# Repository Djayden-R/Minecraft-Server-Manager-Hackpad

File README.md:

# Minecraft Server Manager Hackpad

This is a hackpad designed to control a Minecraft server. It has keys to interact with the server and device: a start key and two keys to switch between modes. It will indicate the state of the server using a status LED and has a screen that displays the live chat and other information about the server.

A demonstraction video can be found [here](https://youtu.be/SgViQMdPCGE) and the build process is documented [here](https://blueprint.hackclub.com/projects/6261).

## Why did I make it?

I have a Minecraft server with my friends and often don't notice it when my friends are online, so I wanted to make this device to show when my friends go online.

Couldn't I just make a Discord bot to ping me when my friends go online? Yeah, but it wouldn't be as fun as making a special device for on my desk that also shows the Minecraft chat live.

## How does it work?

The main logic of checking the server status and the chat isn't done on the Hackpad itself, but instead on the computer it is connected to. To make this work the pc will need to run the ```host.py```. This is going to connect with Home Assistant via MQTT. There is a Home Assistant automation needed that sends the information to the correct MQTT topics.
The program can send the following to the Hackpad (over USB):

- LED [COLOR]
- STATUS [STATUS] [PLAYERS] [VERSION] [UPTIME]
- CHAT [LAST_MESSAGE]
- LOG [LOGLINE]
- MODE [MODE]

The Hackpads task is to handle displaying text on the LCD, handle the LED and send the button presses (either LONG or SHORT):

- START
- MODE_NEXT
- MODE_PREV

Also, about the LED, the hackpad displays different colors in different situations:

- Server off > Red
- Server booting > Blinking Orange
- Server on > Blue
- People online > Blinking Green

## Hardware

Schematic                               |  PCB                   |   3D model
:--------------------------------------:|:----------------------:|:-------------------------:
 |  | 

## BOM

- 3x Cherry MX Switches
- 3x DSA Keycaps
- 1x SK6812 MINI-E LED
- 1x 0.91" 128x32 OLED Display
- 1x XIAO RP2040
- 1x Case (2 printed parts)

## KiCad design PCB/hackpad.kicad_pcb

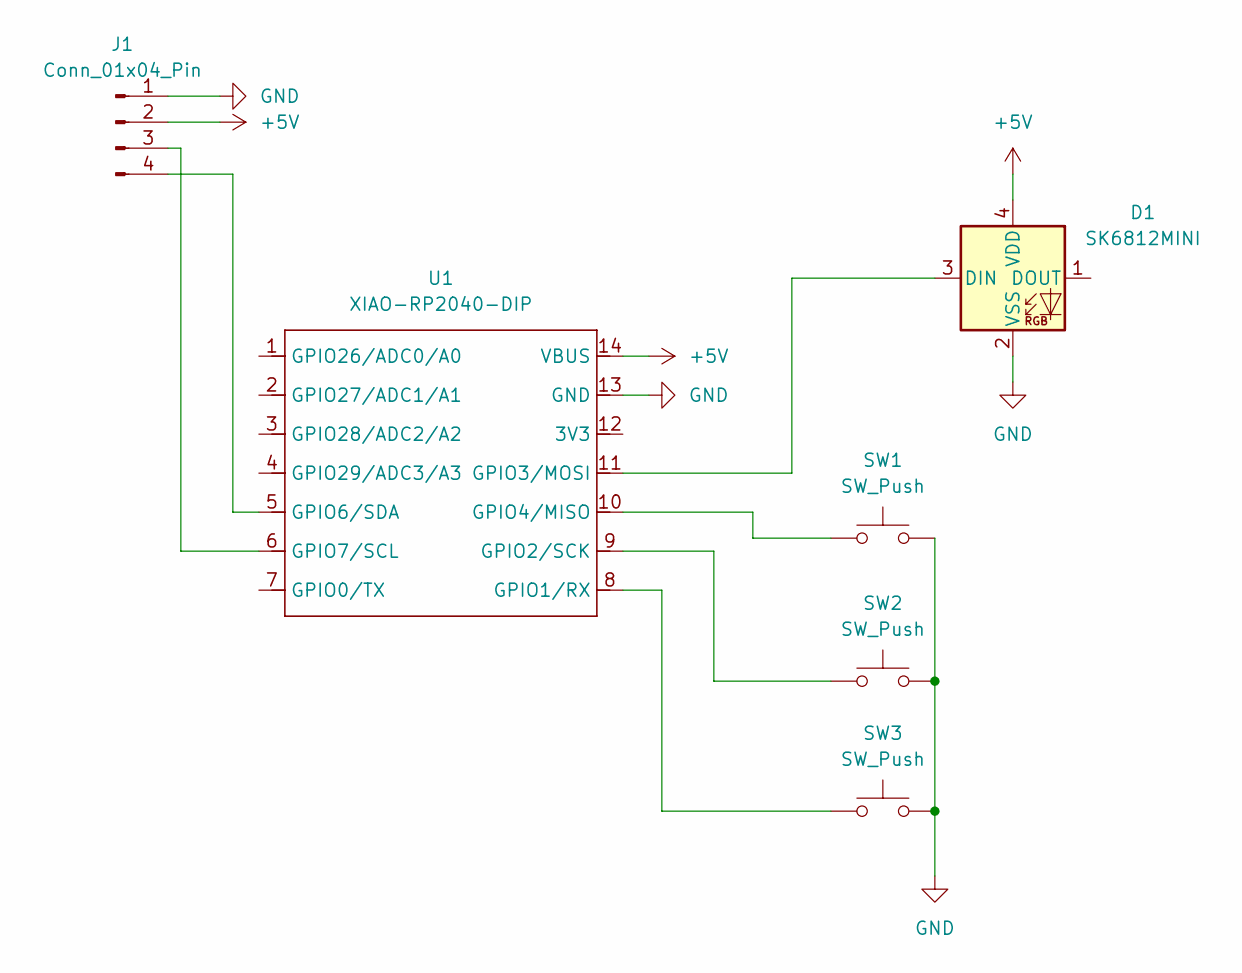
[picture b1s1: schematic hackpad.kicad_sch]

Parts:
D1: SK6812MINI; LED_SK6812MINI_PLCC4_3.5x3.5mm_P1.75mm
J1: Conn_01x04_Pin; SSD1306-0.91-OLED-4pin-128x32
SW1, SW2, SW3: SW_Push; SW_Cherry_MX_1.00u_PCB
U1: XIAO-RP2040-DIP

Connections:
+5V: D1.4 (VDD), J1.2, U1.14 (VBUS)
GND: D1.2 (VSS), J1.1, SW1.2, SW2.2, SW3.2, U1.13 (GND)
unnamed: D1.3 (DIN), U1.11 (GPIO3/MOSI)
unnamed: J1.3, U1.6 (GPIO7/SCL)
unnamed: J1.4, U1.5 (GPIO6/SDA)
unnamed: SW3.1, U1.8 (GPIO1/RX)
unnamed: SW2.1, U1.9 (GPIO2/SCK)
unnamed: SW1.1, U1.10 (GPIO4/MISO)

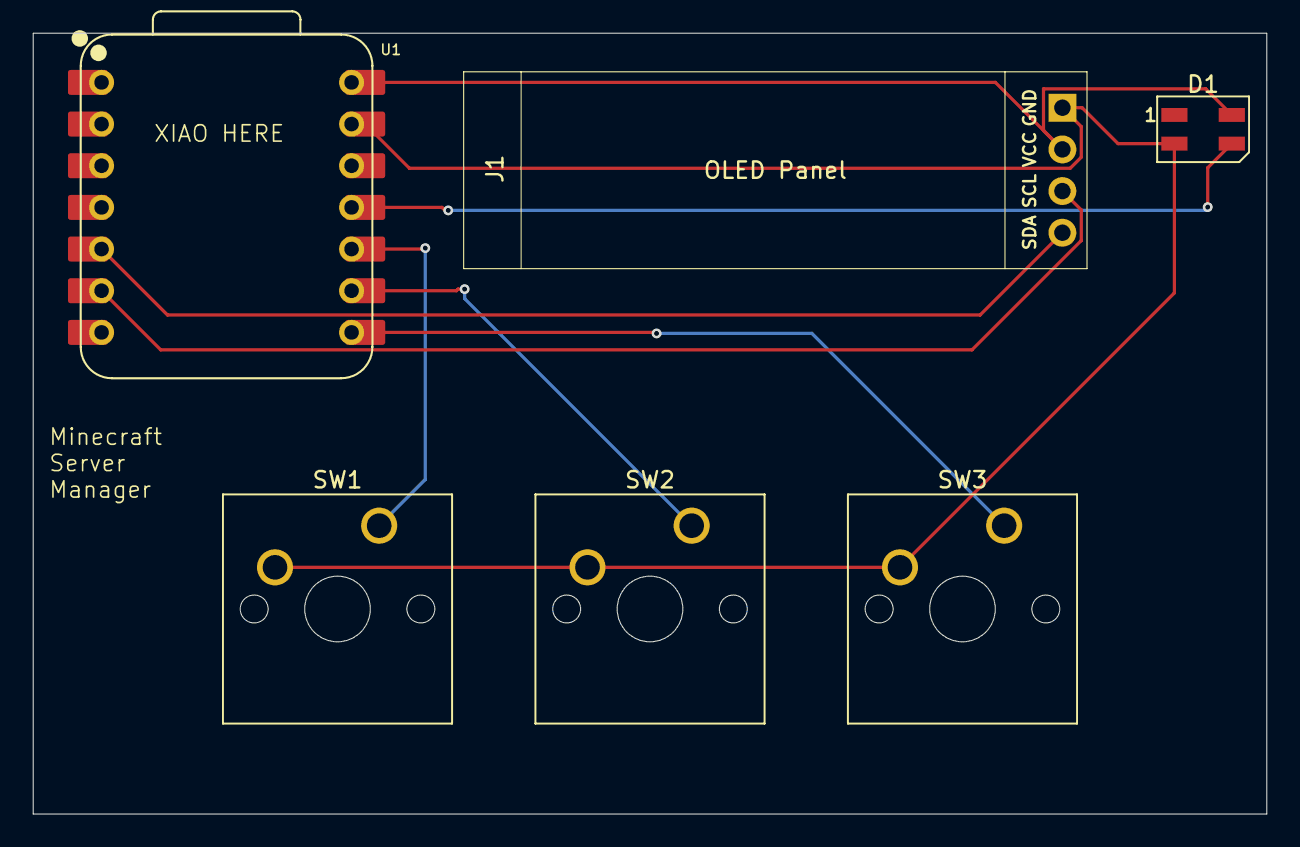
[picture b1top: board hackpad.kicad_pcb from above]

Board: 2 copper layers, 75.2 x 47.6 mm, 6 parts (0 on the bottom side), 8 nets.

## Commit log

2025-12-13 add pcb and 3d model
2025-12-13 add all images for the README
2025-12-13 rename 3d model
2025-12-13 add all libraries for KiCad
2025-12-13 change README
2025-12-14 add .gitignore
2025-12-14 expand README
2025-12-17 reformat README.md
2025-12-17 add placeholders for firmware
2025-12-17 remove files from .gitignore
2025-12-21 add todo.md and .env to .gitignore
2025-12-21 fix typo and structure of README
2025-12-21 make host.py
2025-12-21 make device.py
2025-12-21 add library for LCD screen
2025-12-21 add wait until device connected
2025-12-22 move hackpad code to its own folder
2025-12-22 move PC code to its own folder and replace Home Assistant API with MQTT
2025-12-22 change topic name
2025-12-23 change location of Hacpad folder and add lcd and led to device.py
2025-12-23 add MQTT parsing logic and future functions
2025-12-23 change README.md
2025-12-23 add implementation section to README
2025-12-23 remove STATUS command from MQTT logic
2025-12-23 clarify how Home Assistant connection works
2026-03-28 refactor device.py and host.py for improved functionality and structure
2026-03-28 add extra info to readme
